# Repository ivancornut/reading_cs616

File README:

# Reading CS616

This project aims to read CS616 soil moisture sensors using any microcontroller (arduino Uno in this project)

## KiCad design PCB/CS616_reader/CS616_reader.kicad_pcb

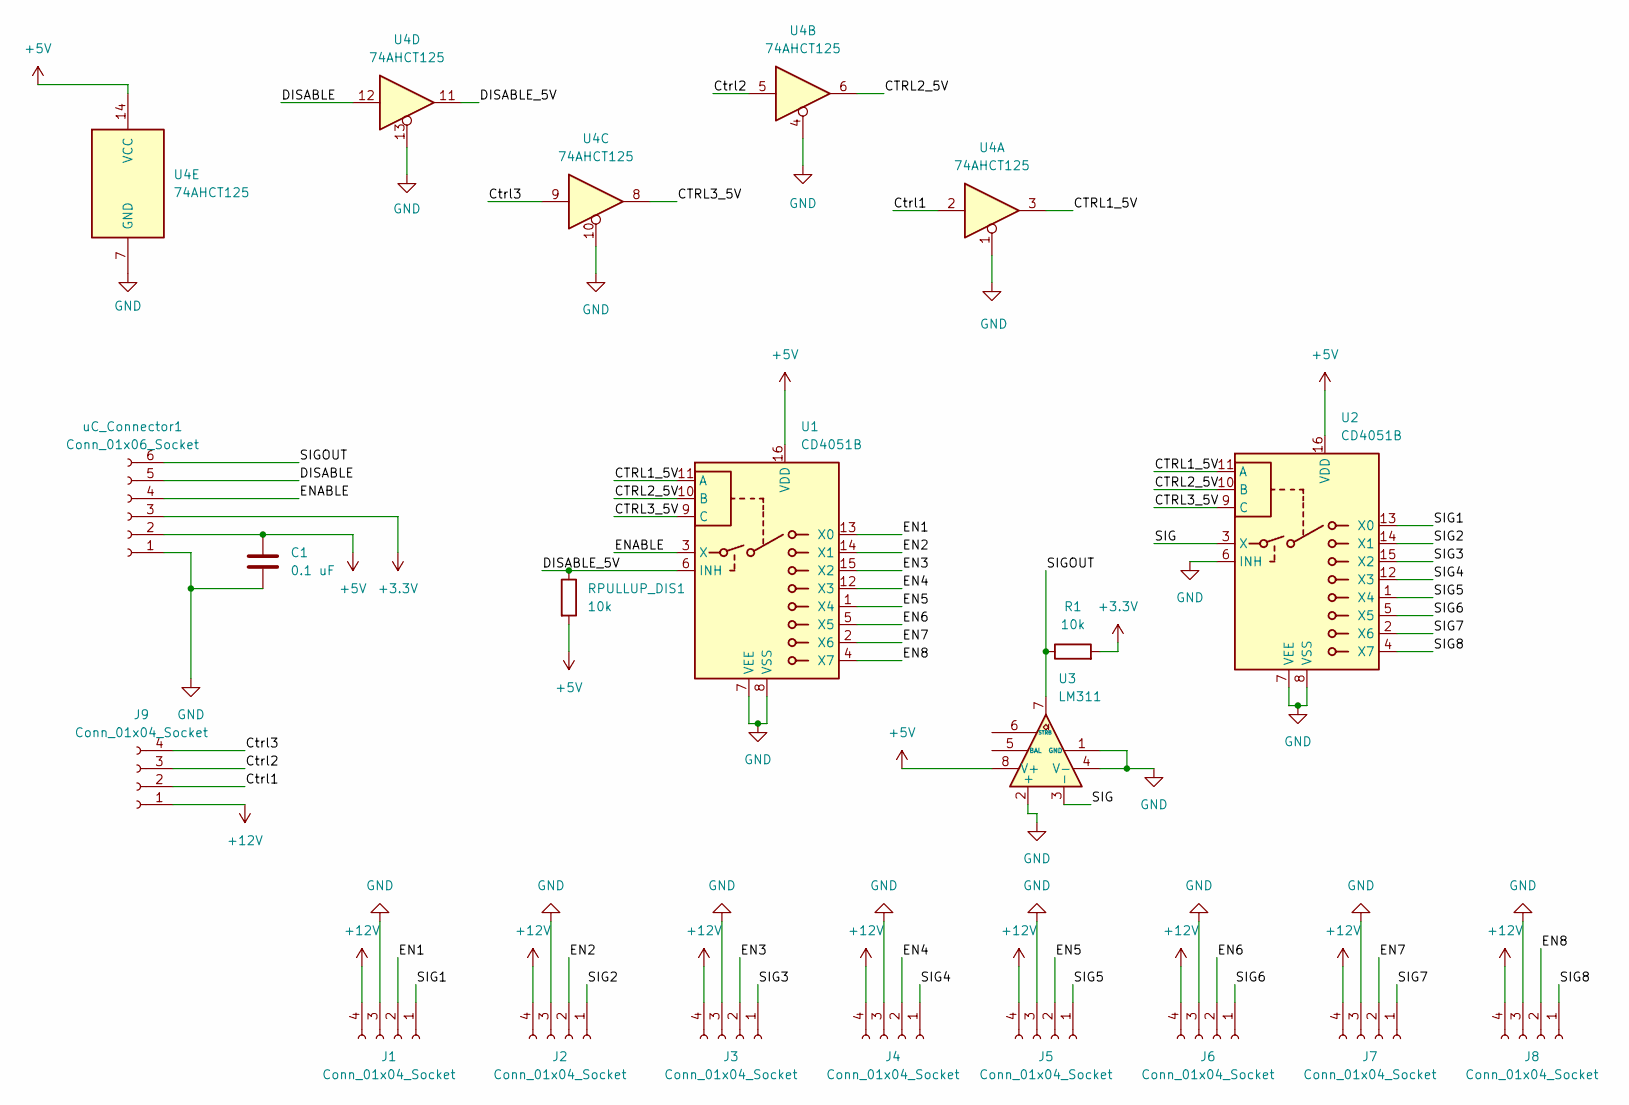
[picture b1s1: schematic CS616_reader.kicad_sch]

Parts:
C1: 0.1 uF; C_1812_4532Metric_Pad1.57x3.40mm_HandSolder
J1, J2, J3, J4, J5, J6, J7, J8, J9: Conn_01x04_Socket; TerminalBlock_Phoenix_MKDS-1,5-4-5.08_1x04_P5.08mm_Horizont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
R1: 10k; R_Axial_DIN0204_L3.6mm_D1.6mm_P5.08mm_Horizontal
RPULLUP_DIS1: 10k; R_Axial_DIN0204_L3.6mm_D1.6mm_P5.08mm_Horizontal
U1, U2: CD4051B; DIP-16_W7.62mm
U3: LM311; CERDIP-8_W7.62mm_SideBrazed
U4: 74AHCT125; DIP-14_W7.62mm
uC_Connector1: Conn_01x06_Socket; TerminalBlock_Phoenix_MKDS-1,5-6-5.08_1x06_P5.08mm_Horizont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

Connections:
+3.3V: R1.2, uC_Connector1.3
+5V: C1.1, RPULLUP_DIS1.2, U1.16 (VDD), U2.16 (VDD), U3.8 (V+), U4.14 (VCC), uC_Connector1.2; also elsewhere on the board
+12V: J1.4, J2.4, J3.4, J4.4, J5.4, J6.4, J7.4, J8.4, J9.1
/CTRL1_5V: U1.11 (A), U2.11 (A), U4.3
/CTRL2_5V: U1.10 (B), U2.10 (B), U4.6
/CTRL3_5V: U1.9 (C), U2.9 (C), U4.8
/Ctrl1: J9.2, U4.2
/Ctrl2: J9.3, U4.5
/Ctrl3: J9.4, U4.9
/DISABLE: U4.12, uC_Connector1.5
/DISABLE_5V: RPULLUP_DIS1.1, U1.6 (INH), U4.11; also elsewhere on the board
/EN1: J1.2, U1.13 (X0)
/EN2: J2.2, U1.14 (X1)
/EN3: J3.2, U1.15 (X2)
/EN4: J4.2, U1.12 (X3)
/EN5: J5.2, U1.1 (X4)
/EN6: J6.2, U1.5 (X5)
/EN7: J7.2, U1.2 (X6)
/EN8: J8.2, U1.4 (X7)
/ENABLE: U1.3 (X), uC_Connector1.4
/SIG: U2.3 (X), U3.3 (-)
/SIG1: J1.1, U2.13 (X0)
/SIG2: J2.1, U2.14 (X1)
/SIG3: J3.1, U2.15 (X2)
/SIG4: J4.1, U2.12 (X3)
/SIG5: J5.1, U2.1 (X4)
/SIG6: J6.1, U2.5 (X5)
/SIG7: J7.1, U2.2 (X6)
/SIG8: J8.1, U2.4 (X7)
/SIGOUT: R1.1, U3.7, uC_Connector1.6
GND: C1.2, J1.3, J2.3, J3.3, J4.3, J5.3, J6.3, J7.3, J8.3, U1.7 (VEE), U1.8 (VSS), U2.6 (INH), U2.7 (VEE), U2.8 (VSS), U3.1 (GND), U3.2 (+), U3.4 (V-), U4.1, U4.4, U4.7 (GND), U4.10, U4.13, uC_Connector1.1

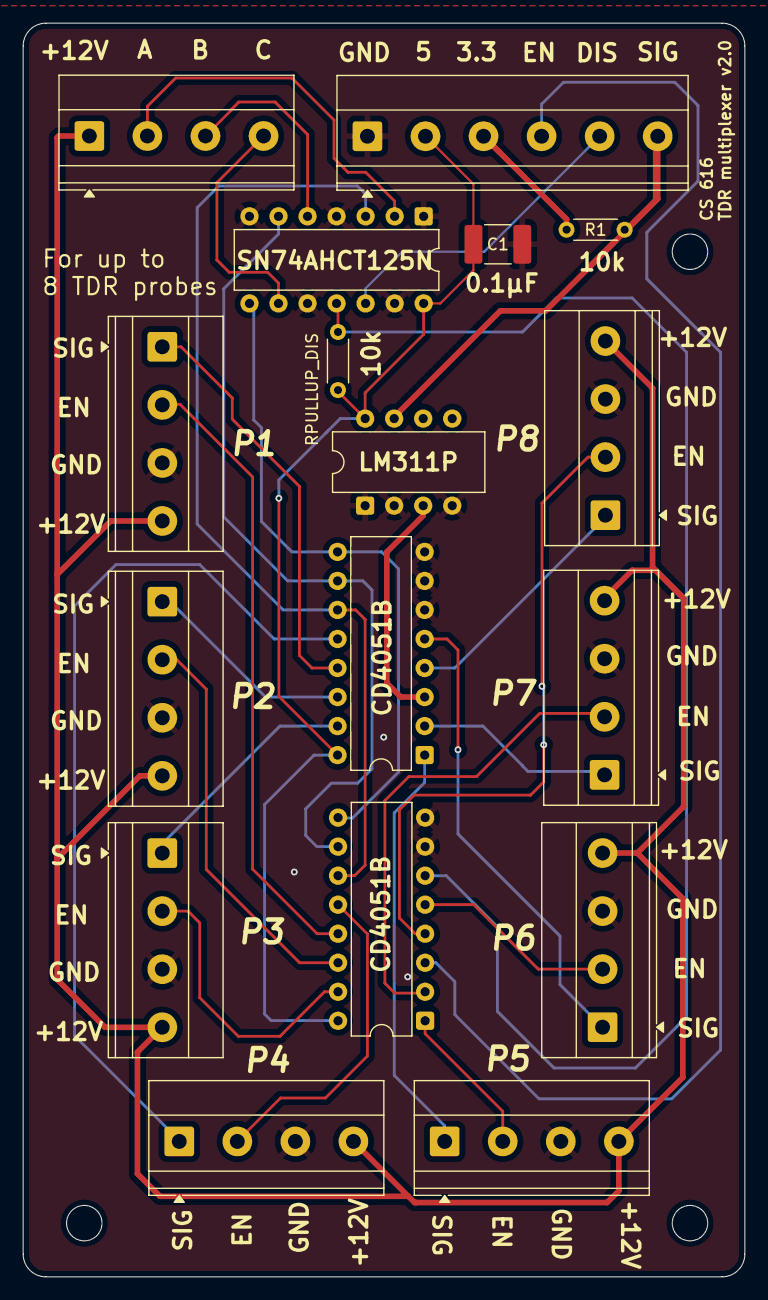
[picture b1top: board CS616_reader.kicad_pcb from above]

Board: 2 copper layers, 63.2 x 109.7 mm, 17 parts (0 on the bottom side), 31 nets.

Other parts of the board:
RPULLUP_DIS: 10k; R_Axial_DIN0204_L3.6mm_D1.6mm_P5.08mm_Horizontal

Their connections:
+5V: RPULLUP_DIS.2; also elsewhere on the board
/DISABLE_5V: RPULLUP_DIS.1; also elsewhere on the board

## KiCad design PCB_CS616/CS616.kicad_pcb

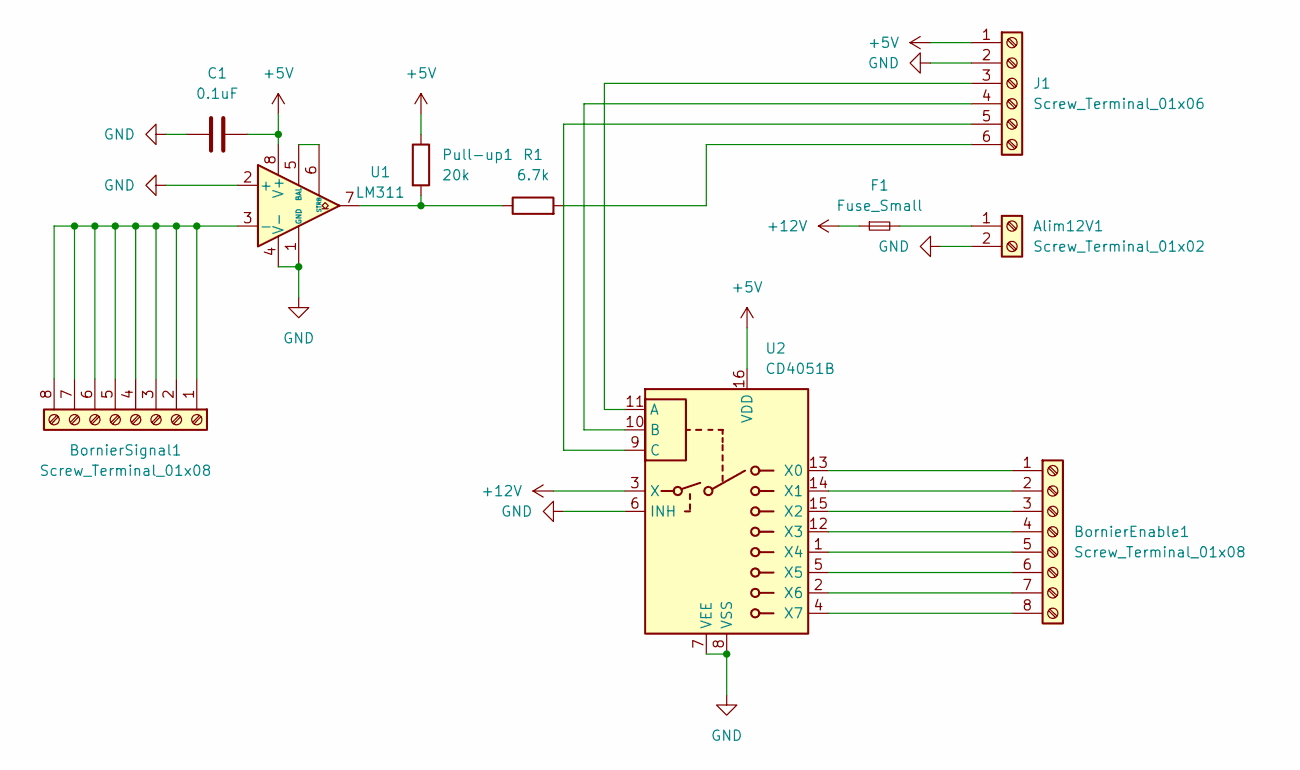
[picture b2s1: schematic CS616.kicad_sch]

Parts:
Alim12V1: Screw_Terminal_01x02; PinSocket_1x02_P2.54mm_Vertical
BornierEnable1: Screw_Terminal_01x08; PinSocket_1x08_P2.54mm_Vertical
BornierSignal1: Screw_Terminal_01x08; PinSocket_1x08_P2.54mm_Vertical
C1: 0.1uF; C_1206_3216Metric
F1: Fuse_Small; Microfuse
J1: Screw_Terminal_01x06; PinSocket_1x06_P2.54mm_Vertical
Pull-up1: 20k; R_1206_3216Metric
R1: 6.7k; R_1206_3216Metric
U1: LM311; DIP794W45P254L959H508Q8
U2: CD4051B; DIP794W45P254L1969H508Q16

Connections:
+5V: C1.1, J1.1, Pull-up1.1, U1.8 (V+), U2.16 (VDD)
+12V: F1.1, U2.3 (X)
GND: Alim12V1.2, C1.2, J1.2, U1.1 (GND), U1.2 (+), U1.4 (V-), U2.6 (INH), U2.7 (VEE), U2.8 (VSS)
unnamed: Alim12V1.1, F1.2
unnamed: BornierEnable1.1, U2.13 (X0)
unnamed: BornierEnable1.2, U2.14 (X1)
unnamed: BornierEnable1.3, U2.15 (X2)
unnamed: BornierEnable1.4, U2.12 (X3)
unnamed: BornierEnable1.5, U2.1 (X4)
unnamed: BornierEnable1.6, U2.5 (X5)
unnamed: BornierEnable1.7, U2.2 (X6)
unnamed: BornierEnable1.8, U2.4 (X7)
unnamed: BornierSignal1.1, BornierSignal1.2, BornierSignal1.3, BornierSignal1.4, BornierSignal1.5, BornierSignal1.6, BornierSignal1.7, BornierSignal1.8, U1.3 (-)
unnamed: J1.3, U2.11 (A)
unnamed: J1.4, U2.10 (B)
unnamed: J1.5, U2.9 (C)
unnamed: J1.6, R1.2
unnamed: Pull-up1.2, R1.1, U1.7
unnamed: U1.5 (BAL), U1.6 (STRB)

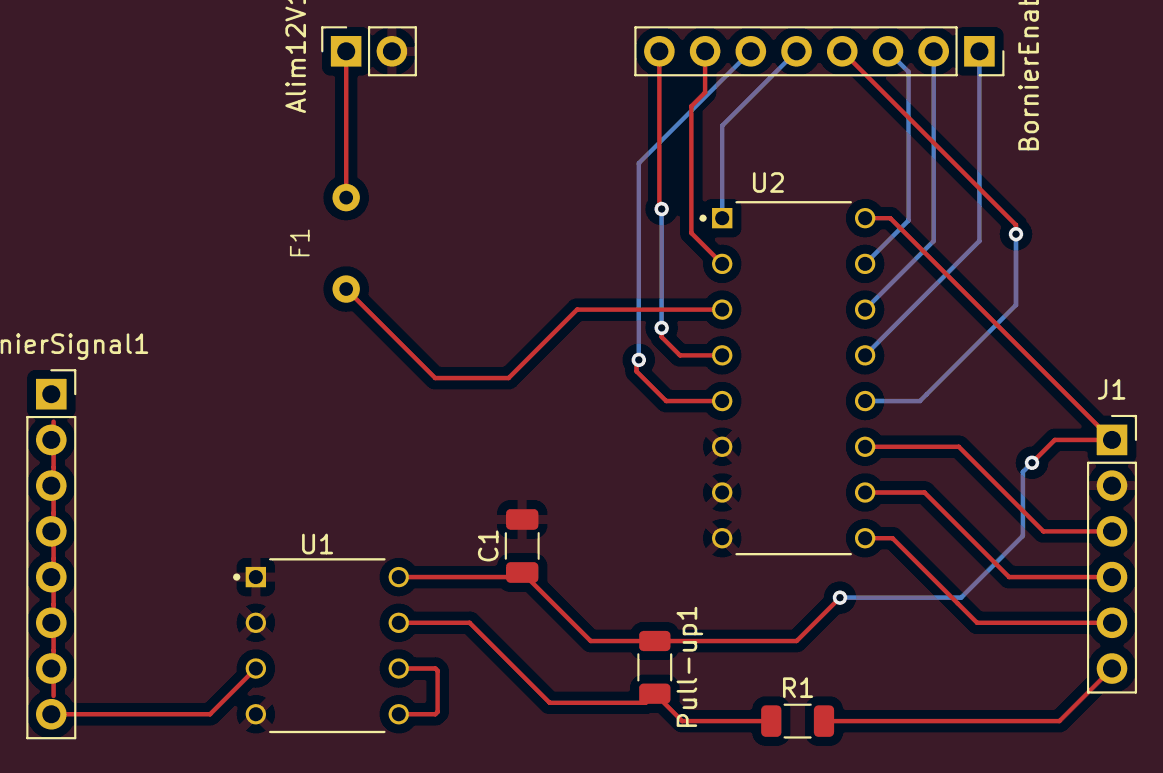
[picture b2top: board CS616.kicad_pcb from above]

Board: 2 copper layers, 10 parts (0 on the bottom side), 19 nets.

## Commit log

2023-08-28 Creation of the repository
2023-08-28 Addition of the simple comparator circuit
2023-08-28 Rename README to README.md
2025-07-28 New scripts
2025-08-05 correction of bugs in datalogger
2025-08-05 Added comments and internal led blink for diagnostics
2025-08-06 Fixed mistake in signal select pin
2025-08-19 Made sleep lightlsleep to preserve batteries
2026-03-02 Improved PCB
2026-03-02 addes small picture for pcb
2026-03-02 Cleaned the repository
2026-03-02 new schematic image
2026-04-22 Added logic level converter to pcb
2026-04-22 Improvements to pcb
